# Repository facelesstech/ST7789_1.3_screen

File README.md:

# ST7789_1.3_screen
ST7789_1.3_screen

Blog post - https://facelesstech.wordpress.com/2019/01/27/1-3-screen-with-raspberry-pi/

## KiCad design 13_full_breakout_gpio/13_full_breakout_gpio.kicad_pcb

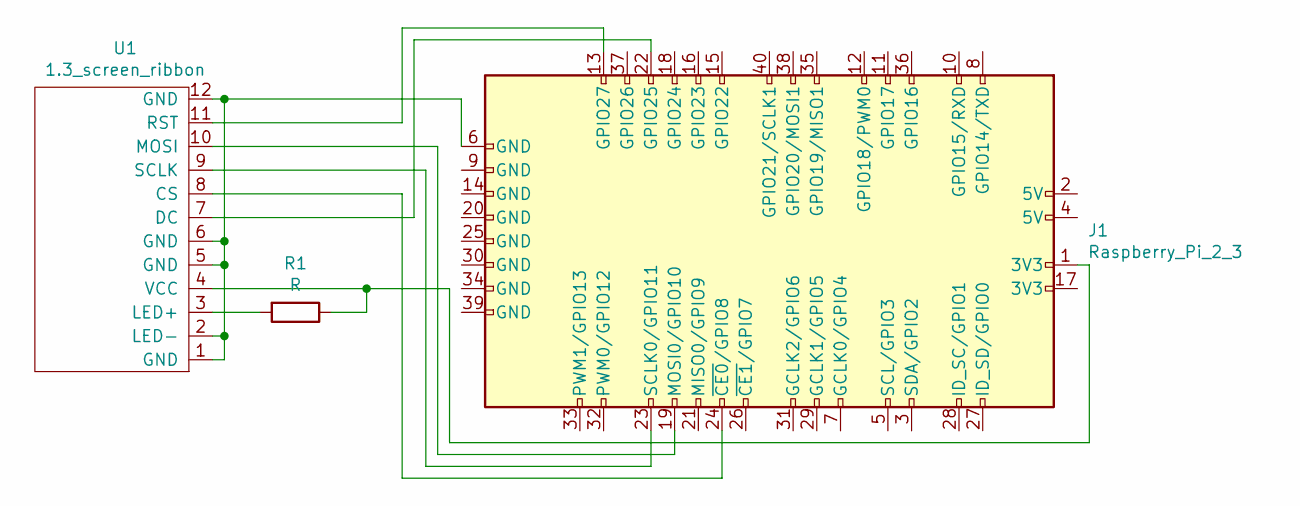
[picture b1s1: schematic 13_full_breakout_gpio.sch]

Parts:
J1: Raspberry_Pi_2_3; raspberry_pi_gpio_smd_custom
R1: R; R_1206_3216Metric
U1: 1.3_screen_ribbon; 1.3_screen_ribbon_breakout

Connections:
unnamed: J1.1 (3V3), R1.1, U1.4 (VCC)
unnamed: J1.6 (GND), U1.1 (GND), U1.2 (LED-), U1.5 (GND), U1.6 (GND), U1.12 (GND)
unnamed: J1.13 (GPIO27), U1.11 (RST)
unnamed: J1.19 (MOSI0/GPIO10), U1.10 (MOSI)
unnamed: J1.22 (GPIO25), U1.7 (DC)
unnamed: J1.23 (SCLK0/GPIO11), U1.9 (SCLK)
unnamed: J1.24 (~CE0~/GPIO8), U1.8 (CS)
unnamed: R1.2, U1.3 (LED+)

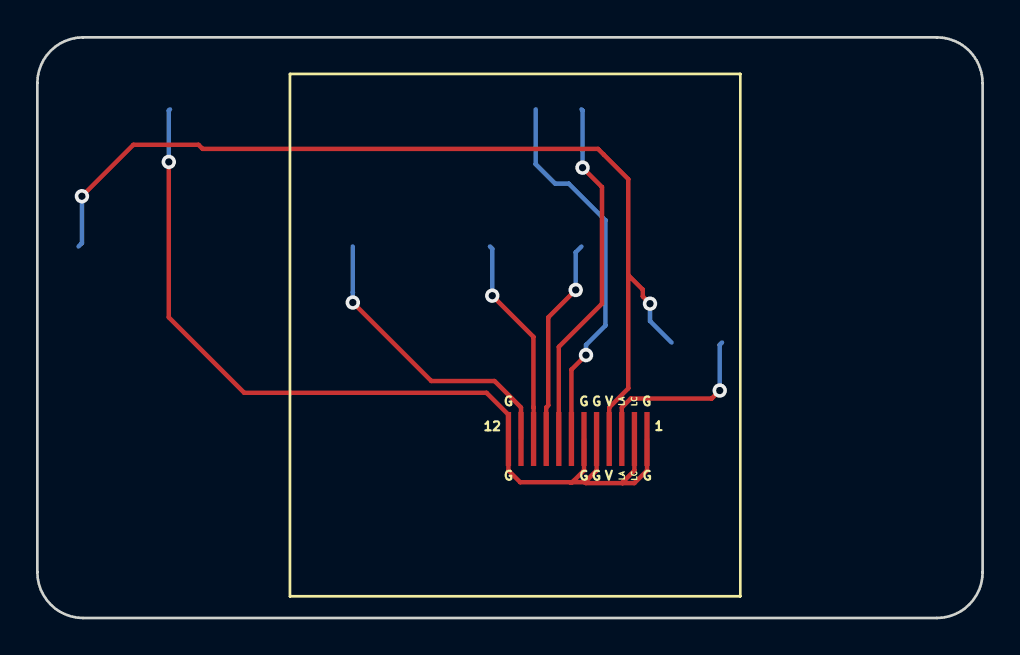
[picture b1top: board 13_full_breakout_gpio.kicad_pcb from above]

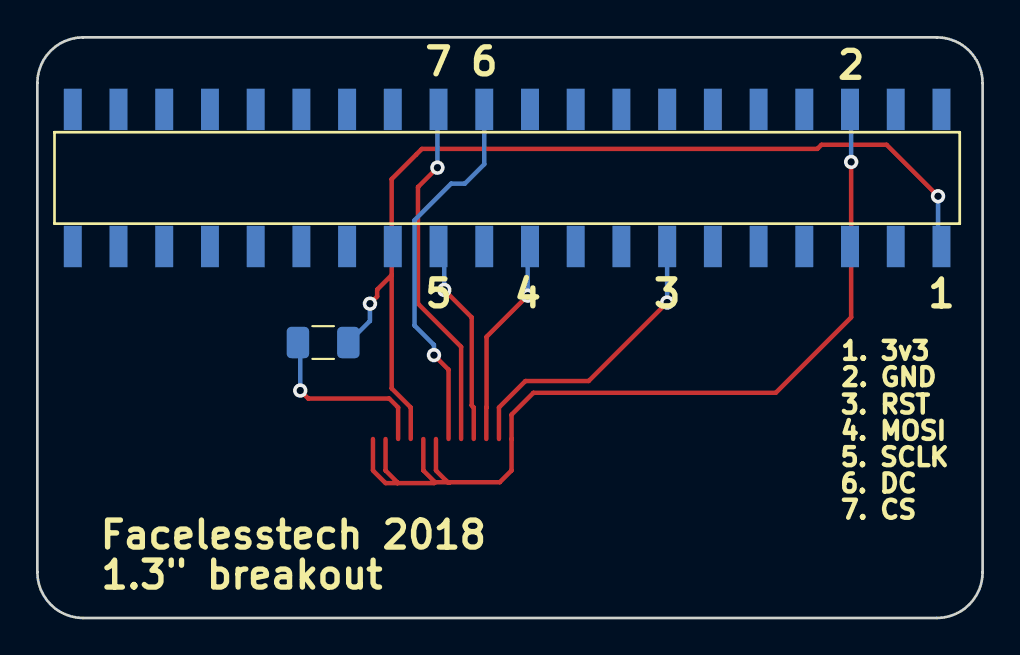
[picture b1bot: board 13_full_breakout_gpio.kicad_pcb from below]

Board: 2 copper layers, 52.5 x 32.3 mm, 3 parts (2 on the bottom side), 8 nets.

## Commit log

2019-01-27 board files
2019-01-27 Blog post links added
